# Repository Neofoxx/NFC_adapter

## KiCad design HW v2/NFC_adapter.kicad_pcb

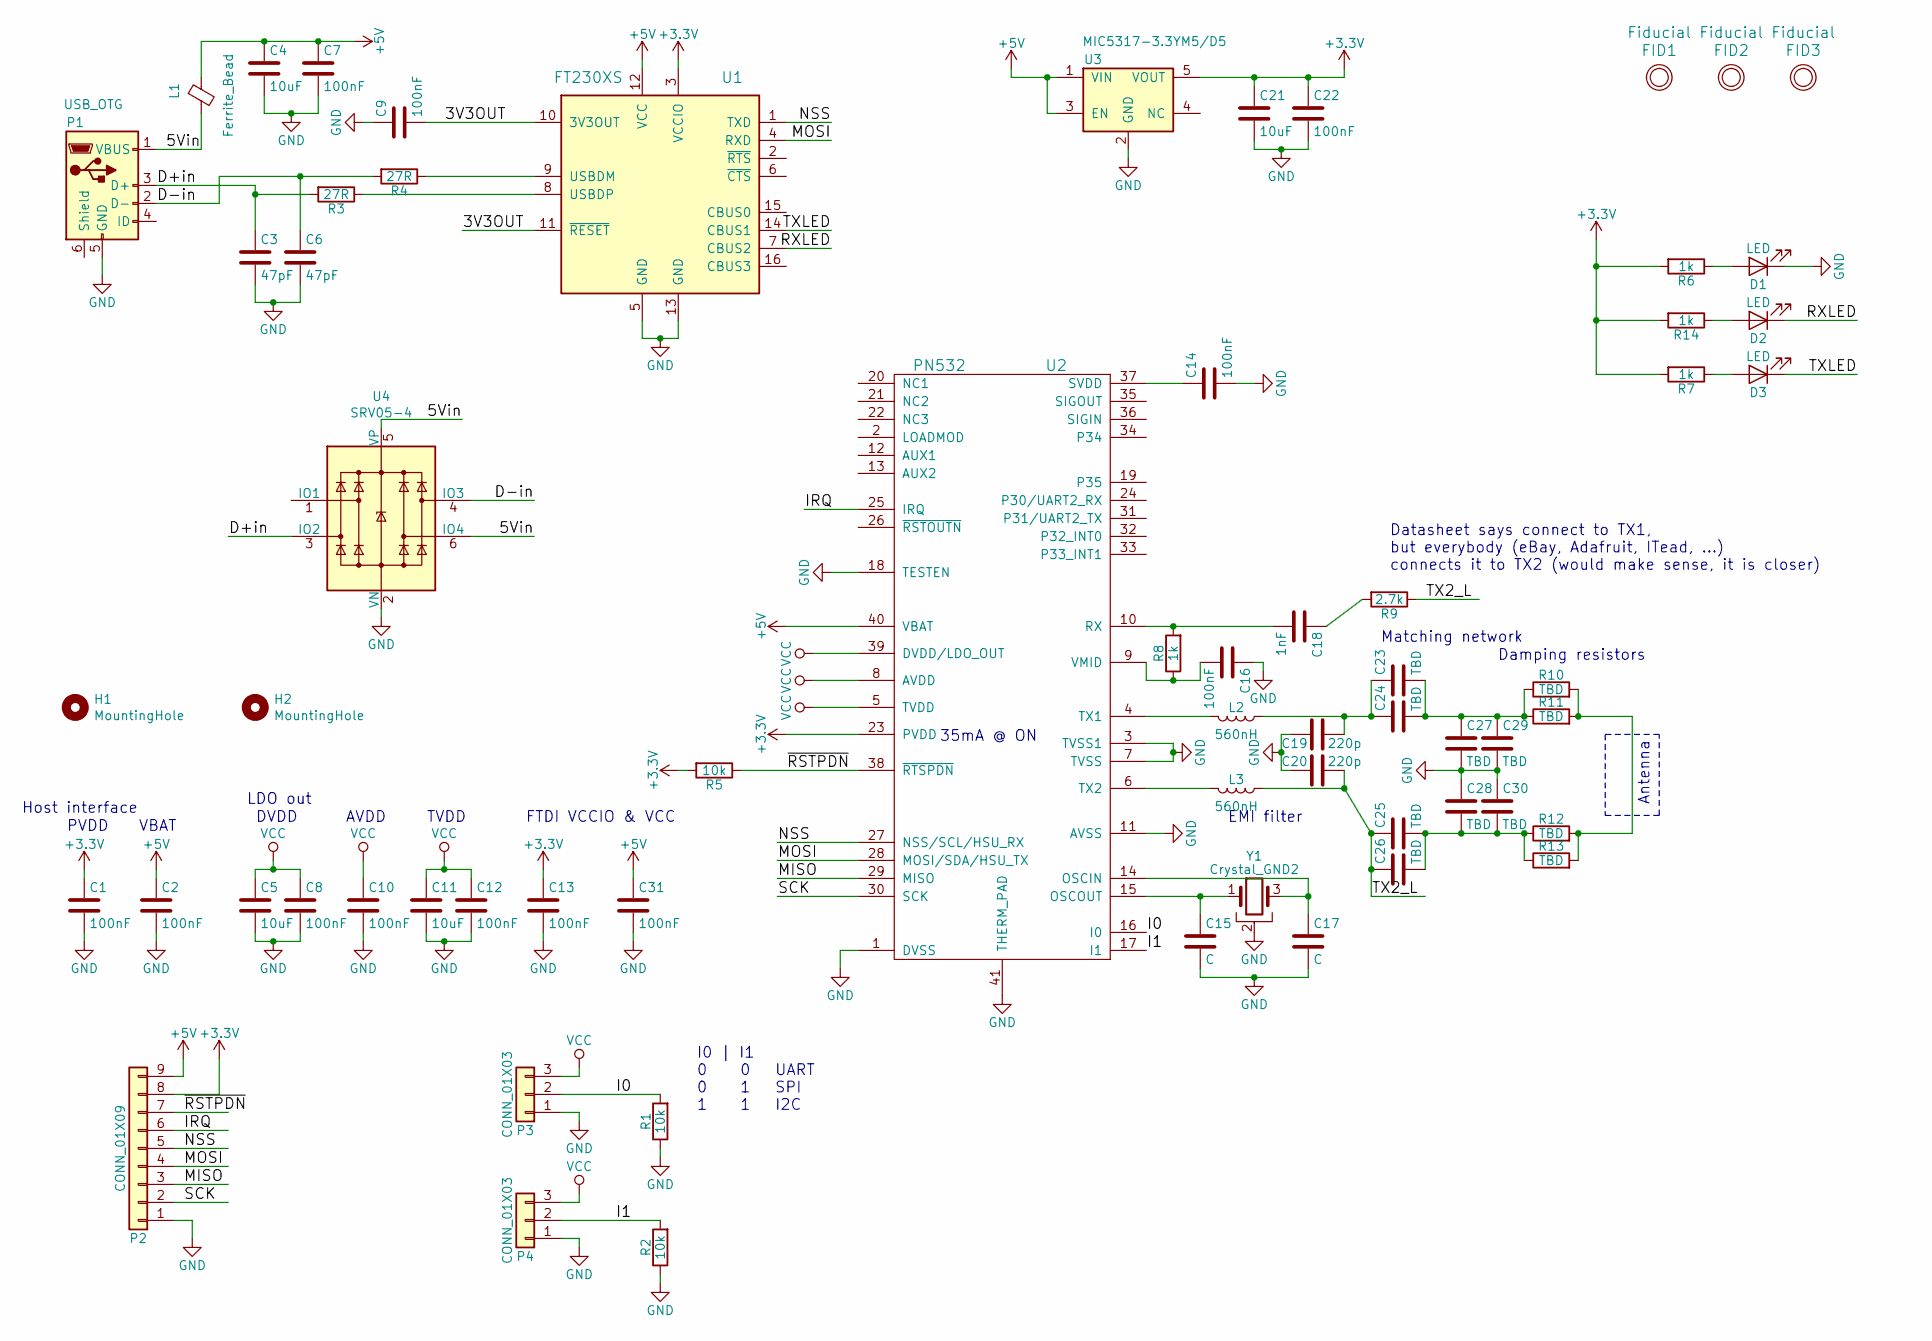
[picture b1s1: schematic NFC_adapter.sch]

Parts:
C1, C2, C7, C8, C9, C10, C12, C13, C14, C16, C22, C31: 100nF; C_0603_1608Metric_Pad1.05x0.95mm_HandSolder
C3, C6: 47pF; C_0603_1608Metric_Pad1.05x0.95mm_HandSolder
C4, C5, C11, C21: 10uF; C_0805_2012Metric_Pad1.15x1.40mm_HandSolder
C15, C17: C; C_0603_1608Metric_Pad1.05x0.95mm_HandSolder
C18: 1nF; C_0603_1608Metric_Pad1.05x0.95mm_HandSolder
C19, C20: 220p; C_0603_1608Metric_Pad1.05x0.95mm_HandSolder
C23, C24, C25, C26, C27, C28, C29, C30: TBD; C_0603_1608Metric_Pad1.05x0.95mm_HandSolder
D1, D2, D3: LED; LED_0603_1608Metric_Pad1.05x0.95mm_HandSolder
FID1, FID2, FID3: Fiducial; FIDUCIAL_1mm
H1, H2: MountingHole; MountingHole_3.5mm
L1: Ferrite_Bead; L_0805_2012Metric_Pad1.15x1.40mm_HandSolder
L2, L3: 560nH; L_1206_3216Metric_Pad1.42x1.75mm_HandSolder
P1: USB_OTG; USB_Micro-B_Amphenol_10103594-0001LF_Horizontal
P2: CONN_01X09; PinSocket_1x09_P2.54mm_Vertical
P3, P4: CONN_01X03; PinSocket_1x03_P2.54mm_Vertical
R1, R2, R5: 10k; R_0603_1608Metric_Pad1.05x0.95mm_HandSolder
R3, R4: 27R; R_0603_1608Metric_Pad1.05x0.95mm_HandSolder
R6, R7, R8, R14: 1k; R_0603_1608Metric_Pad1.05x0.95mm_HandSolder
R9: 2.7k; R_0603_1608Metric_Pad1.05x0.95mm_HandSolder
R10, R11, R12, R13: TBD; R_0603_1608Metric_Pad1.05x0.95mm_HandSolder
U1: FT230XS; SSOP-16_3.9x4.9mm_P0.635mm
U2: PN532; HVQFN40_(SOT618-1)
U3: MIC5317-3.3YM5/D5; SOT-23-5
U4: SRV05-4; SOT-23-6
Y1: Crystal_GND2; TSX-3225

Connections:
+3V3: C1.1, C13.1, C21.1, C22.1, P2.8, R5.2, R6.2, R7.2, R14.2, U1.3 (VCCIO), U2.23 (PVDD), U3.5 (VOUT)
+5V: C2.1, C4.1, C7.1, C31.1, L1.1, P2.9, U1.12 (VCC), U2.40 (VBAT), U3.1 (VIN), U3.3 (EN)
/3V3OUT: C9.2, U1.10 (3V3OUT), U1.11 (~RESET)
/5Vin: L1.2, P1.1 (VBUS), U4.5 (VP), U4.6 (IO4)
/D+in: C3.1, P1.3 (D+), R3.2, U4.3 (IO2)
/D-in: C6.1, P1.2 (D-), R4.2, U4.4 (IO3)
/I0: P3.2, R1.2, U2.16 (I0)
/I1: P4.2, R2.2, U2.17 (I1)
/IRQ: P2.6, U2.25 (IRQ)
/MISO: P2.3, U2.29 (MISO)
/MOSI: P2.4, U1.4 (RXD), U2.28 (MOSI/SDA/HSU_TX)
/NSS: P2.5, U1.1 (TXD), U2.27 (NSS/SCL/HSU_RX)
/RXLED: D2.1 (K), U1.7 (CBUS2)
/SCK: P2.2, U2.30 (SCK)
/TX2_L: C20.2, C25.1, C26.1, L3.1, R9.1
/TXLED: D3.1 (K), U1.14 (CBUS1)
/~RSTPDN~: P2.7, R5.1, U2.38 (~RTSPDN~)
GND: C1.2, C2.2, C3.2, C4.2, C5.2, C6.2, C7.2, C8.2, C9.1, C10.2, C11.2, C12.2, C13.2, C14.2, C15.2, C16.1, C17.2, C19.1, C20.1, C21.2, C22.2, C27.2, C28.1, C29.2, C30.1, C31.2, D1.1 (K), P1.5 (GND), P2.1, P3.1, P4.1, R1.1, R2.1, U1.5 (GND), U1.13 (GND), U2.1 (DVSS), U2.3 (TVSS1), U2.7 (TVSS), U2.11 (AVSS), U2.18 (TESTEN), U2.41 (THERM_PAD), U3.2 (GND), U4.2 (VN), Y1.2
unnamed: C14.1, U2.37 (SVDD)
unnamed: C15.1, U2.15 (OSCOUT), Y1.1
unnamed: C16.2, R8.1, U2.9 (VMID)
unnamed: C17.1, U2.14 (OSCIN), Y1.3
unnamed: C18.1, R9.2
unnamed: C18.2, R8.2, U2.10 (RX)
unnamed: C19.2, C23.1, C24.1, L2.1
unnamed: C23.2, C24.2, C27.1, C29.1, R10.1, R11.1
unnamed: C25.2, C26.2, C28.2, C30.2, R12.1, R13.1
unnamed: D1.2 (A), R6.1
unnamed: D2.2 (A), R14.1
unnamed: D3.2 (A), R7.1
unnamed: L2.2, U2.4 (TX1)
unnamed: L3.2, U2.6 (TX2)
unnamed: R3.1, U1.8 (USBDP)
unnamed: R4.1, U1.9 (USBDM)
unnamed: R10.2, R11.2, R12.2, R13.2
VCC: C5.1, C8.1, C10.1, C11.1, C12.1, P3.3, P4.3, U2.5 (TVDD), U2.8 (AVDD), U2.39 (DVDD/LDO_OUT)

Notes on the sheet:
35mA @ ON
VBAT
EMI filter
Matching network
Damping resistors
DVDD
AVDD
TVDD
PVDD
Host interface
I0 | I1 0 0 UART 0 1 SPI 1 1 I2C
FTDI VCCIO & VCC
Datasheet says connect to TX1, but everybody (eBay, Adafruit, ITead, ...) connects it to TX2 (would make sense, it is closer)
LDO out
Antenna

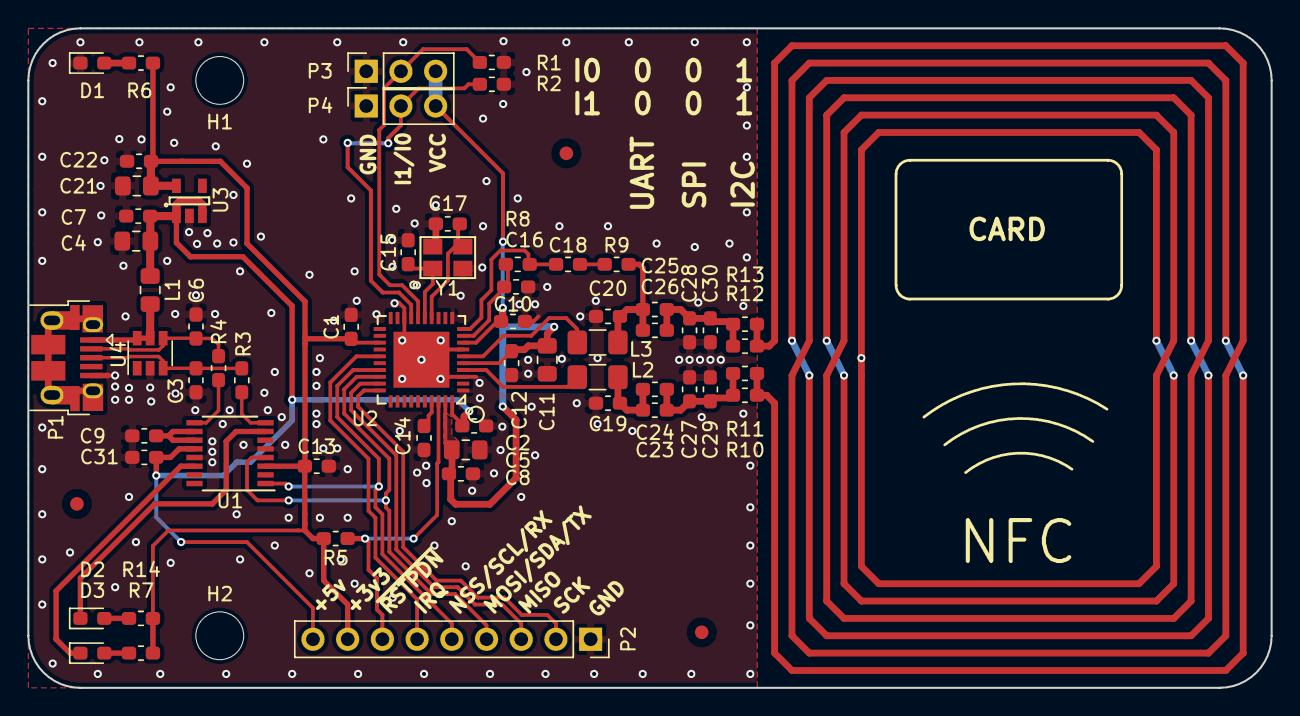
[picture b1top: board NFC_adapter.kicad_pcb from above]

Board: 2 copper layers, 91.0 x 48.3 mm, 65 parts (0 on the bottom side), 36 nets.

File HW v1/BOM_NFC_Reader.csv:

Refs,Value,Footprint,QTY,MFR,MPN,SPR,SPN
C9;C7;C2;C14;C16;C8;C10;C12;C1;C22;C13;C31,100nF,Capacitors_SMD:C_0603,12,,,,
C18,1nF,Capacitors_SMD:C_0603,1,,,,
C19;C20,220p,Capacitors_SMD:C_0603,2,,,,
C3;C6,47pF,Capacitors_SMD:C_0603,2,,,,
C15;C17,C,Capacitors_SMD:C_0603,2,,,,
C24;C25;C27;C28;C26;C23;C29;C30,TBD,Capacitors_SMD:C_0603,8,,,,
C4;C5;C11;C21,10uF,Capacitors_SMD:C_0805,4,,,,
U1,FT230XS,Housings_SSOP:SSOP-16_3.9x4.9mm_Pitch0.635mm,1,,,,
PCB1,PCB,KiCAD library:DP6037_PCB_Outline_NoBackHoles,1,,,,
FID1;FID2;FID3,Fiducial,KiCAD library:FIDUCIAL_1mm,3,,,,
U2,PN532,KiCAD library:HVQFN40_(SOT618-1),1,,,,
P1,USB_OTG,KiCAD library:Micro_USB_-_10103594-0001LF,1,,,,
ANT1,NFC_Antenna,KiCAD library:NFC_Antenna_Symmetric,1,,,,
Y1,Crystal_GND2,KiCAD library:TSX-3225,1,,,,
P5,CONN_01X01,KiCAD library:VIA_STITCH_TENTED_0.3mm,1,,,,
D1;D2;D3;D4,LED,LEDs:LED_0603,4,,,,
P3;P4,CONN_01X03,Pin_Headers:Pin_Header_Straight_1x03,2,,,,
P2,CONN_01X09,Pin_Headers:Pin_Header_Straight_1x09,1,,,,
R5;R1;R2,10k,Resistors_SMD:R_0603,3,,,,
R8;R6;R14,1k,Resistors_SMD:R_0603,3,,,,
R9,2.7k,Resistors_SMD:R_0603,1,,,,
R4;R3,27R,Resistors_SMD:R_0603,2,,,,
R11;R10;R12;R13,TBD,Resistors_SMD:R_0603,4,,,,
L2;L3,560nH,Resistors_SMD:R_0805,2,,,,
L1,Ferrite_Bead,Resistors_SMD:R_0805,1,,,,
U3,MIC5317-3.3YM5/D5,TO_SOT_Packages_SMD:SOT-23-5,1,,,,
